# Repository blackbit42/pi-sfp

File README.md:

# Raspberry Pi SFP Programmer
This is a [KiCad](https://www.kicad.org/) PCB that makes a [Raspberry Pi](https://www.raspberrypi.com/) hat which allows you to read and write the EEPROM content of a [SFP(+) module](https://en.wikipedia.org/wiki/Small_Form-factor_Pluggable).

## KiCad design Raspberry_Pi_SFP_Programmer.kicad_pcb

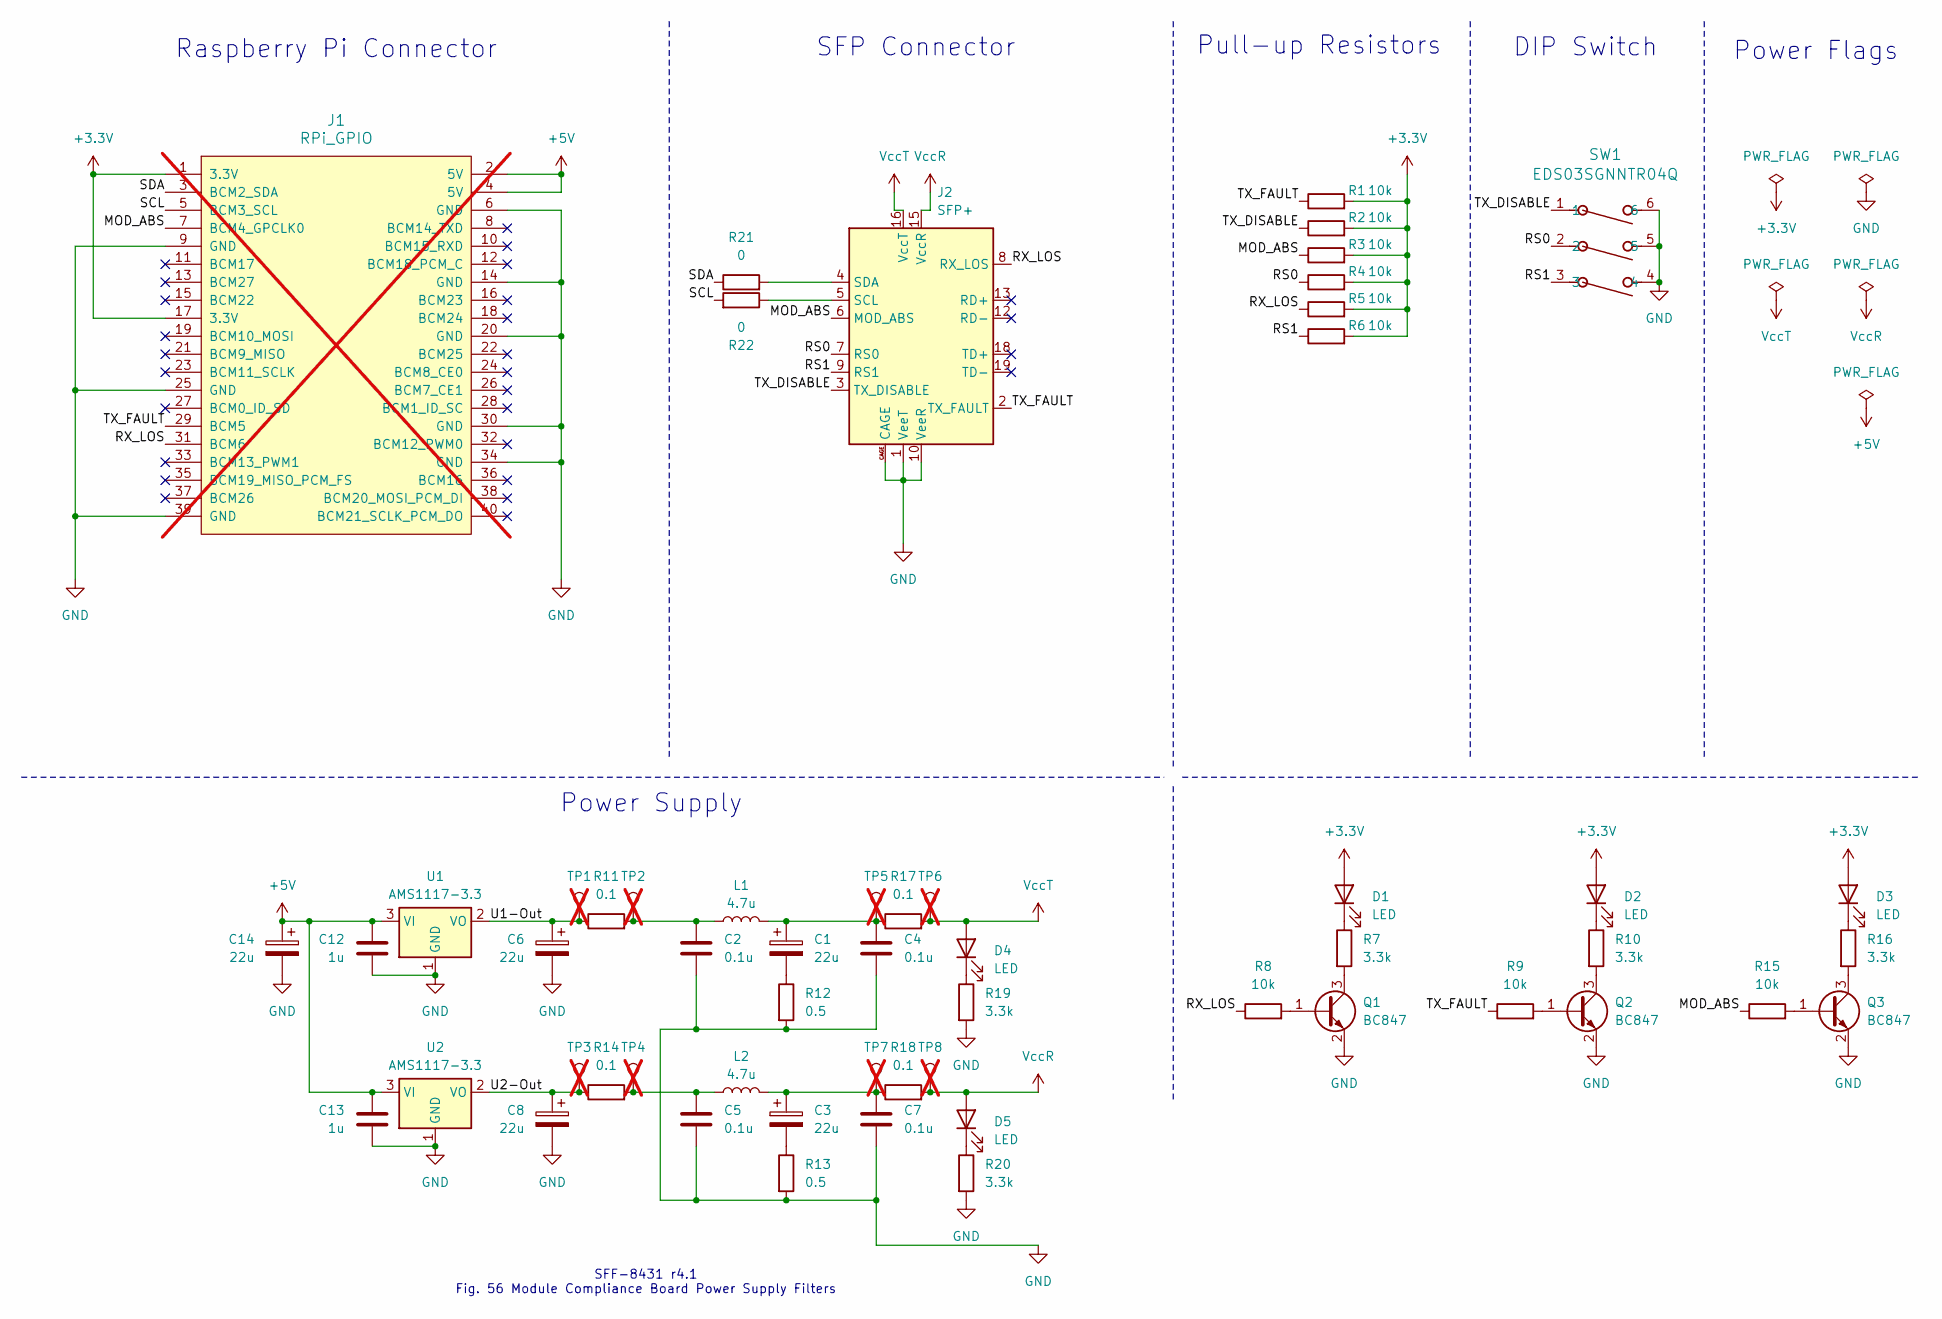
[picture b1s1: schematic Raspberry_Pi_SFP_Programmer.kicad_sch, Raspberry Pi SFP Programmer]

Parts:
C1, C3, C6, C8, C14: 22u; CP_EIA-3528-21_Kemet-B_HandSolder; JLCPCB Part # C110051
C2, C4, C5, C7: 0.1u; C_0402_1005Metric_Pad0.74x0.62mm_HandSolder; JLCPCB Part # C913742
C12, C13: 1u; C_0603_1608Metric_Pad1.08x0.95mm_HandSolder; JLCPCB Part # C519560
D1, D2, D3, D4, D5: LED; LED_0402_1005Metric_Pad0.77x0.64mm_HandSolder; JLCPCB Part # C5123485
J1: RPi_GPIO; RPI_Hat_B+; not fitted
J2: SFP+; Connector_SFP_and_Cage; JLCPCB Part # C42931381
L1, L2: 4.7u; L_0805_2012Metric_Pad1.05x1.20mm_HandSolder; JLCPCB Part # C285965
Q1, Q2, Q3: BC847; SOT-23; JLCPCB Part # C8664
R1, R2, R3, R4, R5, R6, R8, R9, R15: 10k; R_0402_1005Metric_Pad0.72x0.64mm_HandSolder; JLCPCB Part # C60490
R7, R10, R16, R19, R20: 3.3k; R_0402_1005Metric_Pad0.72x0.64mm_HandSolder; JLCPCB Part # C25936
R11, R14, R17, R18: 0.1; R_0805_2012Metric_Pad1.20x1.40mm_HandSolder; JLCPCB Part # C2074770
R12, R13: 0.5; R_0402_1005Metric_Pad0.72x0.64mm_HandSolder; JLCPCB Part # C423160
R21, R22: 0; R_0402_1005Metric_Pad0.72x0.64mm_HandSolder; JLCPCB Part # C17168
SW1: EDS03SGNNTR04Q; SW_2319847_TEC; JLCPCB Part # C5727991
TP1, TP2, TP3, TP4, TP5, TP6, TP7, TP8: TestPoint; TestPoint_Pad_D1.0mm; not fitted
U1, U2: AMS1117-3.3; SOT-223-3_TabPin2; JLCPCB Part # C6186

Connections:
+3.3V: D1.2 (A), D2.2 (A), D3.2 (A), J1.1 (3.3V), J1.17 (3.3V), R1.2, R2.2, R3.2, R4.2, R5.2, R6.2
+5V: C12.2, C13.2, C14.1, J1.2 (5V), J1.4 (5V), U1.3 (VI), U2.3 (VI)
/MOD_ABS: J1.7 (BCM4_GPCLK0), J2.6 (MOD_ABS), R3.1, R15.1
/RS0: J2.7 (RS0), R4.1, SW1.2
/RS1: J2.9 (RS1), R6.1, SW1.3
/RX_LOS: J1.31 (BCM6), J2.8 (RX_LOS), R5.1, R8.1
/SCL: J1.5 (BCM3_SCL), R22.2
/SDA: J1.3 (BCM2_SDA), R21.1
/TX_DISABLE: J2.3 (TX_DISABLE), R2.1, SW1.1
/TX_FAULT: J1.29 (BCM5), J2.2 (TX_FAULT), R1.1, R9.1
/U1-Out: C6.1, R11.1, TP1.1, U1.2 (VO)
/U2-Out: C8.1, R14.1, TP3.1, U2.2 (VO)
GND: C2.2, C4.2, C5.2, C6.2, C7.2, C8.2, C12.1, C13.1, C14.2, J1.6 (GND), J1.9 (GND), J1.14 (GND), J1.20 (GND), J1.25 (GND), J1.30 (GND), J1.34 (GND), J1.39 (GND), J2.1 (VeeT), J2.10 (VeeR), J2.11 (VeeR), J2.14 (VeeR), J2.17 (VeeT), J2.20 (VeeT), J2.CAGE, Q1.2 (E), Q2.2 (E), Q3.2 (E), R12.2, R13.2, R19.2, R20.2, SW1.4, SW1.5, SW1.6, U1.1 (GND), U2.1 (GND)
unnamed: C1.1, C4.1, L1.2, R17.1, TP5.1
unnamed: C1.2, R12.1
unnamed: C2.1, L1.1, R11.2, TP2.1
unnamed: C3.1, C7.1, L2.2, R18.1, TP7.1
unnamed: C3.2, R13.1
unnamed: C5.1, L2.1, R14.2, TP4.1
unnamed: D1.1 (K), R7.1
unnamed: D2.1 (K), R10.1
unnamed: D3.1 (K), R16.1
unnamed: D4.1 (K), R19.1
unnamed: D5.1 (K), R20.1
unnamed: J2.5 (SCL), R22.1
unnamed: J2.4 (SDA), R21.2
unnamed: Q1.1 (B), R8.2
unnamed: Q1.3 (C), R7.2
unnamed: Q2.1 (B), R9.2
unnamed: Q2.3 (C), R10.2
unnamed: Q3.1 (B), R15.2
unnamed: Q3.3 (C), R16.2
VccR: D5.2 (A), J2.15 (VccR), R18.2, TP8.1
VccT: D4.2 (A), J2.16 (VccT), R17.2, TP6.1

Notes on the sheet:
SFP Connector
SFF-8431 r4.1 Fig. 56 Module Compliance Board Power Supply Filters
DIP Switch
Power Flags
Power Supply
Pull-up Resistors
Raspberry Pi Connector

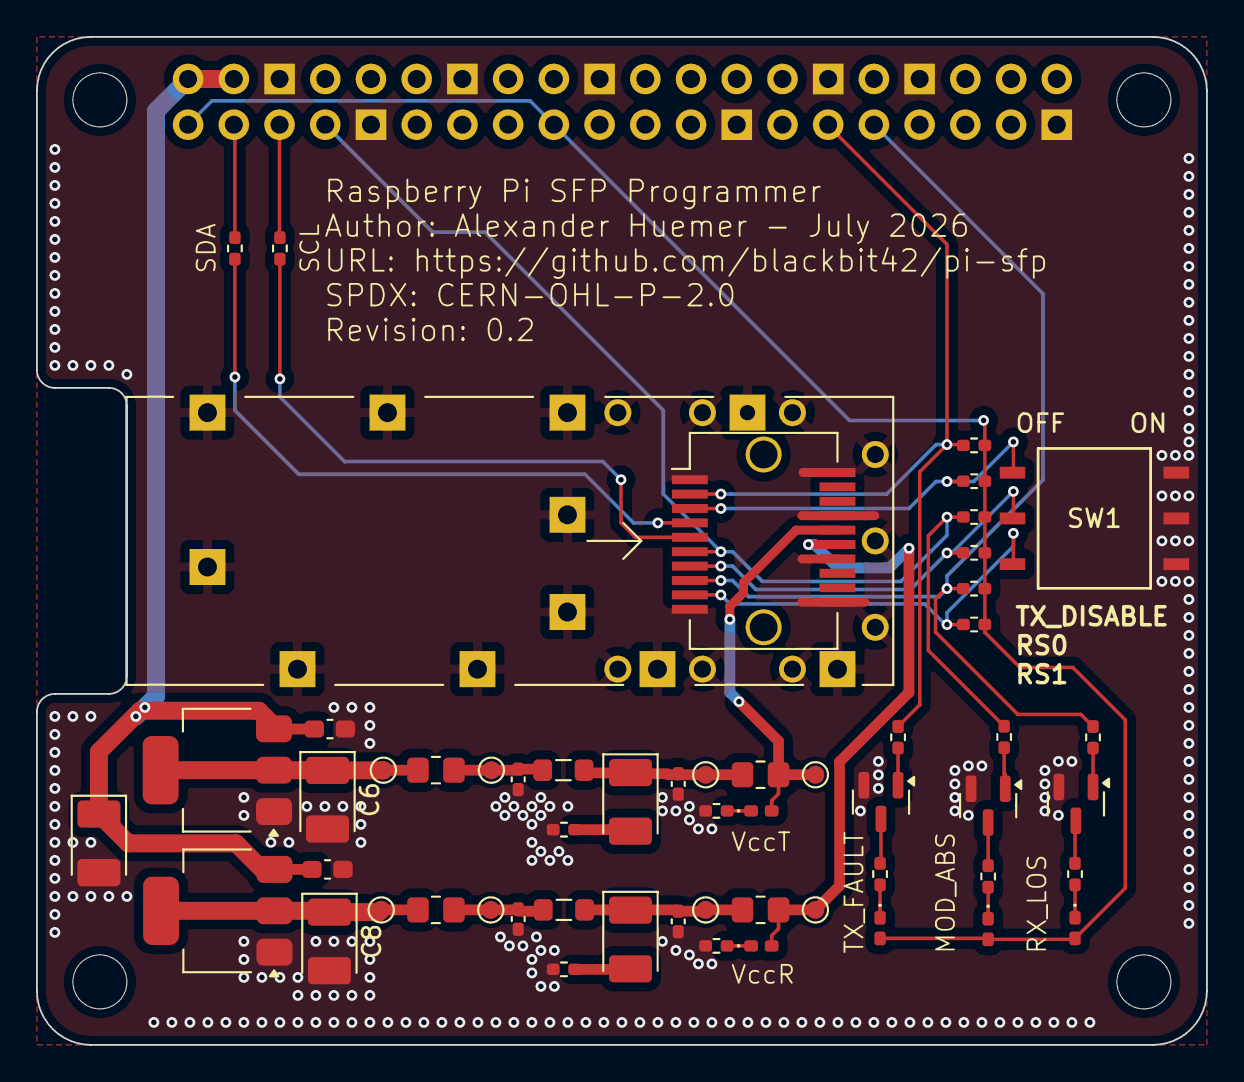
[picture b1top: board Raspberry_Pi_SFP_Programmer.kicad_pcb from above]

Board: 2 copper layers, 65.0 x 56.0 mm, 56 parts (0 on the bottom side), 34 nets.

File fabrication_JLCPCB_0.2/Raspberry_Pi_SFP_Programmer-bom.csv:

"Reference","JLCPCB Part #","Qty","Value","DNP","Exclude from BOM","Exclude from Board","Footprint","Datasheet"
"U1,U2","C6186","2","AMS1117-3.3","","","","Package_TO_SOT_SMD:SOT-223-3_TabPin2","http://www.advanced-monolithic.com/pdf/ds1117.pdf"
"Q1,Q2,Q3","C8664","3","BC847","","","","Package_TO_SOT_SMD:SOT-23","http://www.infineon.com/dgdl/Infineon-BC847SERIES_BC848SERIE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"
"R21,R22","C17168","2","0","","","","Resistor_SMD:R_0402_1005Metric_Pad0.72x0.64mm_HandSolder","~"
"R7,R10,R16,R19,R20","C25936","5","3.3k","","","","Resistor_SMD:R_0402_1005Metric_Pad0.72x0.64mm_HandSolder","~"
"R1,R2,R3,R4,R5,R6,R8,R9,R15","C60490","9","10k","","","","Resistor_SMD:R_0402_1005Metric_Pad0.72x0.64mm_HandSolder","~"
"C1,C3,C6,C8,C14","C110051","5","22u","","","","Capacitor_Tantalum_SMD:CP_EIA-3528-21_Kemet-B_HandSolder","~"
"L1,L2","C285965","2","4.7u","","","","Inductor_SMD:L_0805_2012Metric_Pad1.05x1.20mm_HandSolder","~"
"R12,R13","C423160","2","0.5","","","","Resistor_SMD:R_0402_1005Metric_Pad0.72x0.64mm_HandSolder","~"
"C12,C13","C519560","2","1u","","","","Capacitor_SMD:C_0603_1608Metric_Pad1.08x0.95mm_HandSolder","~"
"C2,C4,C5,C7","C913742","4","0.1u","","","","Capacitor_SMD:C_0402_1005Metric_Pad0.74x0.62mm_HandSolder","~"
"R11,R14,R17,R18","C2074770","4","0.1","","","","Resistor_SMD:R_0805_2012Metric_Pad1.20x1.40mm_HandSolder","~"
"D1,D2,D3,D4,D5","C5123485","5","LED","","","","LED_SMD:LED_0402_1005Metric_Pad0.77x0.64mm_HandSolder","~"
"SW1","C5727991","1","EDS03SGNNTR04Q","","","","Raspberry_Pi_SFP_Programmer:SW_2319847_TEC","EDS03SGNNTR04Q"
"J2","C42931381","1","SFP+","","","","Connector:Connector_SFP_and_Cage","https://members.snia.org/document/dl/25892"

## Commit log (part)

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2025-05-24 root-commit
2025-06-13 Rev. 0.1
2025-12-18 Exclude backup files from version control
2025-12-18 Fix PSU cap

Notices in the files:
Raspberry_Pi_SFP_Programmer.kicad_pcb:
License: CERN Open Hardware Licence Version 2 - Permissive
SPDX: CERN-OHL-P-2.0
